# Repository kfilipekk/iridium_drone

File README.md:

# NAVCORE-SoOP

A 46.5 × 47.2 mm, 6-layer STM32H743 flight controller that navigates without GPS using the Doppler shift of Iridium satellites. It runs ArduPilot with a MatekH743-compatible pinout and also carries the avionics for a TVC rocket lander. Made by Krystian Filipek for my GNSS-denied drone and the Cambridge University Spaceflight Lander Challenge.

<div align="center">

</div>

## Features

### Iridium Navigation
Optical flow and visual-inertial odometry drift without bound over long flights. Iridium NEXT satellites orbit at ~780 km and ~7.5 km/s and transmit continuously at 1616-1626.5 MHz, so the Doppler shift of their bursts gives an absolute position with bounded error (typically 100-200 m) that complements the faster inertial sensors.

- **L-band Receiver** - MAX2112 direct-conversion tuner and OPA2374 baseband filter into the ADCs
- **Antenna Feed** - MMCX port with a current-limited 5 V feed for the active antenna, reported as open, ok or short
- **On-board Navigation** - burst detection, SGP4 orbits and the position solve run on the H743 and feed ArduPilot's EKF as a GPS
- **Spoofing Check** - the real GPS is checked against the Iridium-only fix before it is trusted

### Hardware
| Subsystem | Components |
|-----------|------------|
| MCU | STM32H743VIT6, Cortex-M7 @ 480 MHz, 2 MB flash, 1 MB RAM |
| IMUs | ICM-42688-P (SPI1) and ICM-42605 (SPI4) on a separate low-noise 3.3 V rail |
| Barometer | MS5611 on I2C2 |
| Storage | W25Q128 flash for the orbit catalogue, microSD over SDIO |
| Power | 3S-5S input, TVS and reverse-polarity protection, two LMR33630 bucks (5 V 1.6 A system, 5 V 2.1 A payload) and three 3.3 V LDOs |
| Connectors | Latching JST-GH on every cable port, two servo headers, MMCX, USB-C, TC2030 SWD pads |
| Protection | ESD clamp on every cable-facing signal, series resistors on the motor, telemetry, current, lidar and servo lines |

### Layer Stackup
```
F.Cu:   RF, crystals, MCU fanout
In1.Cu: Continuous ground plane
In2.Cu: SPI, SDIO and I2C
In3.Cu: UARTs, PWM and slow I/O
In4.Cu: Power planes (+5V, +5V_PAYLOAD, +3V3, VBAT)
B.Cu:   Sensors, RF receiver, DroneCAN, bucks
```

### Supported Platforms
- **GNSS-denied Quadcopter** - 30.5 mm stack mount, DShot ESC on `J2`, optical flow on `J14`, lidar on `J11`, companion computer on `J21`, DroneCAN on `J6`
- **TVC Rocket Lander** - two servo outputs (`J17`, `J23`) on the payload rail and 6-DoF logging to microSD

### How It Compares
| | NAVCORE-SoOP | SpeedyBee F405 V4 | Matek H743-SLIM V3 | Pixhawk 6C |
|---|---|---|---|---|
| MCU | STM32H743 | STM32F405 | STM32H743 | STM32H743 + F103 |
| IMUs | ICM-42688-P + ICM-42605 | ICM-42688-P | ICM-42688-P + ICM-42605 | ICM-42688-P + BMI088 |
| Input | 3-5S | 3-6S | 2-8S | power module |
| Port ESD | every cable signal | none stated | none stated | none stated |
| Position without GNSS | Iridium Doppler, 100-200 m | none | none | none |

It has no OSD and no 9-12 V video rail, and it takes 5S at most.

## Getting Started

### Prerequisites
- **KiCad 9** with the `pcbnew` Python module
- **Python 3** with `pip install -r requirements.txt`
- **[kicad-tools](https://github.com/kfilipekk/kicad-tools)** cloned to `~/Code/kicad-tools`, or set `KICAD_TOOLS` - the checks any board needs live there
- **ArduPilot toolchain** for the firmware (`tools/build_firmware.sh` pins Copter-4.7.0)

### Checking the Board
1. Clone the repository:
   ```bash
   git clone https://github.com/kfilipekk/iridium_drone.git
   cd iridium_drone
   ```

2. Run every check (about 15 minutes):
   ```bash
   python3 tools/preflight.py
   ```

3. Or run one check on its own:
   ```bash
   python3 tools/check_board.py connectors
   python3 ~/Code/kicad-tools/fab.py stock
   ```

4. Build the firmware:
   ```bash
   bash tools/build_firmware.sh
   ```

### Ordering
The JLCPCB files are in `fab/`: the Gerber and drill bundle, BOM, pick-and-place and schematic PDF. Order 6 layers, 1 oz outer copper, no impedance control, epoxy-filled and capped vias, ENIG, and top and bottom assembly.

## Repository Structure

```
├── NAVCORE-SoOP.kicad_pcb   # PCB
├── NAVCORE-SoOP.kicad_sch   # Schematic, generated from tools/design.py
├── fab/                     # JLCPCB order files
├── firmware/                # ArduPilot hwdef, the SoOP backend and the on-board navigation
├── tools/                   # Design model, generators and checks
├── cad/                     # OpenSCAD airframe and clearance models
├── sim/                     # SPICE decks for the analogue blocks
├── sitl/                    # ArduPilot SITL scenarios
└── libraries/               # Footprint and symbol libraries
```

## Applications

I made this project to explore:
- Navigation from signals of opportunity instead of GPS
- Six-layer mixed-signal PCB design with an RF front end
- ArduPilot drivers and EKF integration
- Automated checks for a hardware design

## Future Plans

- Bench-test the Iridium receive chain with the HC610 antenna
- Rev E: a third IMU, 6S input and a 9-12 V video rail

<div align="center">

Developed by [kfilipekk](https://github.com/kfilipekk)

</div>

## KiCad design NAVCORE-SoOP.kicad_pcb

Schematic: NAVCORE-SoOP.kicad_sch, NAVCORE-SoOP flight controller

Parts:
C1, C2, C3, C4, C5, C10, C12, C14, C21, C30, C31, C32, C33, C34, C35, C36, C41, C43, C44, C46, C49, C50, C57, C60, C65, C68, C74, C88, C89, C90, C94, C95, C96: 100n; C_0402_1005Metric; LCSC C1525
C6, C7: 4u7; C_0805_2012Metric; LCSC C354262
C8, C9, C29: 2u2; C_0402_1005Metric; LCSC C12530
C11, C13, C26, C27, C28, C51, C67, C75, C78, C79, C80: 1u; C_0402_1005Metric; LCSC C52923
C15, C16: 30p; C_0402_1005Metric; LCSC C107004
C17, C18: 10u; C_1206_3216Metric; LCSC C13585
C19, C66: 100n; C_0402_1005Metric; LCSC C307331
C22: 100u; C_1206_3216Metric; LCSC C883598
C23, C69, C70: 47u; C_1206_3216Metric; LCSC C96123
C42: 1u; C_0805_2012Metric; LCSC C28323
C45, C93: 10u; C_0805_2012Metric; LCSC C15850
C52: 33p; C_0402_1005Metric; LCSC C1562
C56, C98, C99: 100p; C_0201_0603Metric; LCSC C62550
C58, C73: 10n; C_0402_1005Metric; LCSC C15195
C59, C97: 100n; C_0201_0603Metric; LCSC C76939
C61, C63: 47n; C_0402_1005Metric; LCSC C82219
C76, C77: 100p; C_0402_1005Metric; LCSC C1546
C81, C84, C86: 1n; C_0402_1005Metric; LCSC C1523
C91: 10p; C_0402_1005Metric; LCSC C32949
C92: 22u; C_1206_3216Metric; LCSC C12891
C100, C101: 1n; C_0201_0603Metric; LCSC C710792
D1: SMBJ22CA; SMB_L4.6-W3.6-LS5.3-RD; LCSC C113994
D2: BLUE; LED_0603_1608Metric; LCSC C965807
D3: GREEN; LED_0603_1608Metric; LCSC C965804
D4: 1N4148W; SOD-123F_L2.7-W1.6-LS3.8-RD; LCSC C81598
D6: PESD2CANFD24LT; SOT-23-3_L2.9-W1.6-P1.90-LS2.8-BR; LCSC C6952426
D7, D9: PESD5V0C1BSF; DSN0603-2_L0.6-W0.3-P0.40-BI; LCSC C477955
D8: SMF9.0A; SOD-123FL_L2.7-W1.8-LS3.7-RD; LCSC C1973343
D10: B2020WS; SOD-323_L1.7-W1.3-LS2.7-RD; LCSC C77284
DZ1: BZT52C15; SOD-123_L2.7-W1.6-LS3.7-RD; LCSC C173427
D_USB: B5819W; SOD-123_L2.7-W1.6-LS3.7-RD-1; LCSC C8598
FID1, FID2, FID3: Fiducial; Fiducial_1mm_Mask2mm
J1: USB-C; USB-C-SMD_TYPE-C-16PIN-2MD-073; LCSC C2765186
J2: ESC 8P; CONN-TH_SM08B-SRSS-TB-LF-SN; LCSC C160407
J3: GPS+I2C; CONN-SMD_XY-SM06B-GHS-TB; LCSC C51940119
J5: RC IN; CONN-SMD_4P-P1.25_BX-GH1.25-4PWT; LCSC C18077720
J6: CAN 4P; CONN-SMD_4P-P1.25_BX-GH1.25-4PWT; LCSC C18077720
J8: microSD; TF-SMD_TF-01A; LCSC C91145
J9: I2C 4P; CONN-SMD_4P-P1.25_BX-GH1.25-4PWT; LCSC C18077720
J11: SERIAL2 4P; CONN-SMD_4P-P1.25_BX-GH1.25-4PWT; LCSC C18077720
J12: MMCX-KWE-90; MMCX-TH_DL-MMCX-KWE-90; LCSC C2894793
J14: FLOW 6P; CONN-SMD_XY-SM06B-GHS-TB; LCSC C51940119
J17: SERVO1; HDR-SMD_3P-P2.54-H-M_KH-2.54PH-1X3P-L13.5-WT; LCSC C20610212
J19: TC2030-NL; Tag-Connect_TC2030-IDC-NL_2x03_P1.27mm_Vertical
J21: COMPANION; CONN-SMD_XY-SM06B-GHS-TB; LCSC C51940119
J22: PAYLOAD 5V; CONN-TH_SM03B-GHS-TB-LF-SN; LCSC C514175
J23: SERVO2; HDR-SMD_3P-P2.54-H-M_KH-2.54PH-1X3P-L13.5-WT; LCSC C20610212
L1: 600R@100MHz; L_0805_2012Metric; LCSC C1017
L2: 10uH; L_APV_ANR4030; LCSC C167879
L5: 10uH; L_APV_ANR5040; LCSC C354610
L6: 27nH; L0402; LCSC C113111
P151: LED_5V; TestPoint_Pad_1.5x1.5mm
P152: LED_DIN; TestPoint_Pad_1.5x1.5mm
P153: LED_GND; TestPoint_Pad_1.5x1.5mm
P161: BUZ_5V; TestPoint_Pad_1.5x1.5mm
P162: BUZ_OUT; TestPoint_Pad_1.5x1.5mm
P163: BUZ_GND; TestPoint_Pad_1.5x1.5mm
PF1, PF2, PF3, PF4, PF5, PF6, PF7, PF9, PF10, PF11: PWR_FLAG
PF8: PWR_FLAG; not fitted
Q1, Q3: AO3400A; SOT-23-3_L2.9-W1.3-P1.90-LS2.4-BR; LCSC C20917
Q4: WST4041; SOT-23-3_L2.9-W1.3-P1.90-LS2.4-BR; LCSC C148357
R1, R14, R39, R45, R48, R49, R50, R51, R52, R53, R59, R60: 10k; R_0402_1005Metric; LCSC C25744
R4, R6, R40, R42, R46: 100k; R_0402_1005Metric; LCSC C25741
R5, R41: 22k; R_0402_1005Metric; LCSC C25768
R7, R43: 24k9; R_0402_1005Metric; LCSC C25874
R9, R10, R12, R31, R36, R37, R47, R58: 4k7; R_0402_1005Metric; LCSC C25900
R11: 4k7; R_0201_0603Metric; LCSC C270346
R15: 120R; R_0402_1005Metric; LCSC C25079; not fitted
R16, R17: 5k1; R_0402_1005Metric; LCSC C25905
R18: 10k; R_0603_1608Metric; LCSC C25804
R19, R20, R21, R35: 1k; R_0402_1005Metric; LCSC C11702
R22, R23, R24, R25, R26: 47k; R_0402_1005Metric; LCSC C25792
R27: 47k; R_0402_1005Metric; LCSC C25792; not fitted
R28, R29: 0R; R_0402_1005Metric; LCSC C17168
R34: 330R; R_0402_1005Metric; LCSC C25104
R38, R70, R72, R73, R74, R75: 100R; R_0402_1005Metric; LCSC C25076
R57: 470R; R_0402_1005Metric; LCSC C25117
R61: 210k; R_0402_1005Metric; LCSC C58827
R62: 2R2; R_0402_1005Metric; LCSC C1881139
R71: 2k2; R_0402_1005Metric; LCSC C25879
R76, R77: 680R; R_0201_0603Metric; LCSC C473509
RN1: 33R x4; R_Array_Convex_4x0402; LCSC C25501
SW1: BOOT; SW_SPST_B3U-1000P; LCSC C231329
SW2: RESET; SW_SPST_B3U-1000P; LCSC C231329
TP3: PWM5; TestPoint_Pad_1.5x1.5mm
TP4: PWM6; TestPoint_Pad_1.5x1.5mm
TP9: SOOP_I_OUT; TestPoint_Pad_1.5x1.5mm
TP10: SOOP_Q_OUT; TestPoint_Pad_1.5x1.5mm
U1: STM32H743VIT6; LQFP-100_L14.0-W14.0-P0.50-LS16.0-BL; LCSC C5271084
U2: ICM-45686; LGA-14_L3.0-W2.5-P0.50-TL; LCSC C22459454
U3: ICM-42605; LGA-14_L3.0-W2.5-P0.50-TL; LCSC C2655099
U4: MS5611; SENSORS-SMD_MS5611-01BA03; LCSC C15639
U5: W25Q128JVPIQ; WSON-8-1EP_6x5mm_P1.27mm_EP3.4x4.3mm; LCSC C190862
U8, U20: LMR33630A; VQFN-12_L3.0-W2.0-P0.65-BL_TI_RNX; LCSC C2861505
U9: TLV75733P; SOT-23-5_L2.9-W1.6-P0.95-LS2.8-BL-EP; LCSC C22399950
U10: TLV75533; SOT-23-5_L3.0-W1.7-P0.95-LS2.8-BR; LCSC C404027
U11: SN65HVD230; SOIC-8_L4.9-W3.9-P1.27-LS6.0-BL; LCSC C12084
U12: USBLC6-2SC6; SOT-23-6_L2.9-W1.6-P0.95-LS2.8-BL; LCSC C2687116
U13: MAX2112; TQFN-28_L5.0-W5.0-P0.50-BL-EP3.3; LCSC C596391
U14: OPA2374; SOP-8_L4.9-W3.9-P1.27-LS6.0-BL; LCSC C444392
U17: 74LVC1G17; SOT-23-5_L3.0-W1.7-P0.95-LS2.8-BR; LCSC C7836
U19: TMP119; DSBGA-6_L1.5-W1.0-R2-C3-P0.40-BL; LCSC C22428347
U21: XC6206P332MR; SOT-23-3_L2.9-W1.6-P1.90-LS2.8-BR; LCSC C5446
U22, U23: SRV05-4; SOT-23-6_L2.9-W1.6-P0.95-LS2.8-BR; LCSC C6454456
U24: AP22653; SOT-23-6_L2.9-W1.6-P0.95-LS2.8-BR; LCSC C2158037
U25: INA180A2; SOT-23-5_L3.0-W1.7-P0.95-LS2.8-BL; LCSC C192764
U26, U27, U28, U29, U30: TPD4E05U06; USON-10_2.5x1.0mm_P0.5mm; LCSC C138714
U31: LM66100; SC-70-6_L2.0-W1.3-P0.65-LS2.1-BL; LCSC C2869734
Y1: 8MHz; CRYSTAL-SMD_4P-L3.2-W2.5-BL; LCSC C2682774
Y2: 25MHz TCXO; OSC-SMD_4P-L3.2-W2.5-BL; LCSC C19674258

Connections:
+3V3A: C29.1, C30.1, C31.1, C32.1, C33.1, C34.1, C35.1, C59.1, C97.1, PF4.1, R11.1, R28.1, R52.1, U2.5 (VDDIO), U2.8 (VDD), U3.5 (VDDIO), U3.8 (VDD), U4.1 (VDD), U4.2 (PS), U10.5 (OUT), U14.8 (VCC+), Y2.4 (VCC)
+3V3_CAN: C41.1, C67.1, U11.3 (VCC), U21.2 (Vout)
+5V_BIAS: C90.1, C91.1, C93.1, L6.1, R62.2, U25.4 (IN-)
+5V_BIAS_SW: C96.1, R62.1, U24.6 (OUT), U25.3 (IN+)
ANT_CURRENT: U1.17 (PC2_C), U25.1 (OUT)
ANT_IN: C52.1, D7.1 (A1), J12.1 (SIG), L6.2
BATT_V_DIV: C43.1, R18.2, R19.1, U1.15 (PC0)
BB_VREF: C75.1, C98.2, C99.2, R49.2, R51.2, R52.2, R53.1
BIAS_EN: R59.2, U1.33 (PC5), U24.3 (EN/EN#)
BIAS_FAULT: R60.2, U1.57 (PD10), U24.4 (FAULT#)
BIAS_ILIM: R61.1, U24.5 (ILIM)
BOOT0: R1.1, SW1.2, U1.94 (BOOT0)
BUCK_BOOT: C21.1, U8.4 (BOOT)
BUCK_EN: R4.2, R5.1, U8.9 (EN)
BUCK_FB: R6.2, R7.1, U8.7 (FB)
BUCK_PAYLOAD_BOOT: C68.1, U20.4 (BOOT)
BUCK_PAYLOAD_EN: C73.1, Q3.3 (D), R40.2, R41.1, U20.9 (EN)
BUCK_PAYLOAD_FB: R42.2, R43.1, U20.7 (FB)
BUCK_PAYLOAD_PH: C68.2, L5.1, U20.3 (NC), U20.12 (SW)
BUCK_PAYLOAD_VCC: C79.1, U20.5 (VCC)
BUCK_PH: C21.2, L2.1, U8.3 (NC), U8.12 (SW)
BUCK_VCC: C78.1, U8.5 (VCC)
BUZZER: R38.1, U1.77 (PA15)
BUZZ_DRAIN: D4.2 (A), P162.1, Q1.3 (D)
BUZZ_GATE: Q1.1 (G), R38.2, R39.1
CAN1_RX: U1.81 (PD0), U11.4 (R)
CAN1_SILENT: R14.1, U1.84 (PD3), U11.8 (RS)
CAN1_TX: U1.82 (PD1), U11.1 (D)
CANH: D6.1 (C), J6.2, R15.1, U11.7 (CANH)
CANL: D6.2 (C), J6.3, R15.2, U11.6 (CANL)
CC1: J1.A5 (CC1), R16.1
CC2: J1.B5 (CC2), R17.1
CPOUT: C81.1, R34.1, R57.1, U13.12 (CPOUT)
ESC_CUR: C44.1, R71.2, U1.16 (PC1)
ESC_CUR_J: J2.7, R71.1, U27.1 (D1+), U27.10 (NC)
ESC_TEL: R70.2, U1.97 (PE0)
ESC_TEL_J: J2.8, R70.1, U27.2 (D1-), U27.9 (NC)
EXT_CS1: J14.5, U1.7 (PC13), U29.5 (D2-), U29.6 (NC)
EXT_CS2: U1.1 (PE2), U5.1 (#CS)
GC1: R35.2, R58.2, U13.5 (GC1)
GND: C1.2, C2.2, C3.2, C4.2, C5.2, C6.2, C7.2, C8.2, C9.2, C10.2, C11.2, C12.2, C13.2, C14.2, C15.2, C16.2, C17.2, C18.2, C19.2, C22.2, C23.2, C26.2, C27.2, C28.2, C29.2, C30.2, C31.2, C32.2, C33.2, C34.2, C35.2, C36.2, C41.2, C42.2, C43.2, C44.2, C45.2, C46.2, C49.2, C50.2, C51.2, C56.2, C57.2, C59.2, C60.2, C65.2, C66.2, C67.2, C69.2, C70.2, C73.2, C74.2, C75.2, C78.2, C79.2, C80.2, C81.2, C84.2, C86.2, C88.2, C89.2, C90.2, C91.2, C92.2, C93.2, C94.2, C95.2, C96.2, C97.2, C100.2, C101.2, D1.2 (A2), D6.3 (A), D7.2 (A2), D8.2, D9.2 (A2), J1.13 (EH), J1.14 (EH), J1.A1B12 (GND), J1.B1A12 (GND), J2.1, J2.9, J2.10, J3.6, J3.7, J3.8, J5.4, J5.5, J5.6, J6.4, J6.5, J6.6, J8.6 (VSS), J8.10 (GND), J8.11 (GND), J8.12 (GND), J8.13 (GND), J9.4, J9.5, J9.6, J11.4, J11.5, J11.6, J12.2 (GND), J12.3 (GND), J12.4 (GND), J12.5 (GND), J14.6, J14.7, J14.8, J17.3, J19.5, J19.6, J21.6, J21.7, J21.8, J22.2, J22.3, J22.4, J22.5, J23.3, P153.1, P163.1, PF5.1, Q1.2 (S), Q3.2 (S), R1.2, R5.2, R7.2, R14.2, R16.2, R17.2, R19.2, R29.1, R35.1, R39.2, R41.2, R43.2, R45.2, R46.2, R53.2, R61.2, SW2.2, U1.10 (VSS), U1.19 (VSSA), U1.26 (VSS), U1.49 (VSS), U1.74 (VSS), U1.99 (VSS), U2.6 (GND), U2.7 (RESV), U3.6 (GND), U3.7 (RESV), U4.3 (GND), U4.4 (CSB), U4.5 (CSB), U5.4 (GND), U5.9 (EP), U8.1 (PGND), U8.6 (AGND), U8.11 (PGND), U9.2 (GND), U9.6 (EP), U10.2 (GND), U11.2 (GND), U12.2 (GND), U13.3 (GND), U13.10 (GNDTUNE), U13.11 (GNDSYN), U13.29 (EP), U14.4 (VCC-), U17.3 (GND), U19.B2 (GND), U19.C1 (ADD0), U20.1 (PGND), U20.6 (AGND), U20.11 (PGND), U21.1 (GND), U22.2 (GND), U23.2 (GND), U24.2 (GND), U25.2 (GND), U26.3 (GND), U26.8 (GND), U27.3 (GND), U27.8 (GND), U28.3 (GND), U28.8 (GND), U29.3 (GND), U29.8 (GND), U30.3 (GND), U30.8 (GND), U31.2 (GND), U31.4 (NC), U31.5 (ST), Y1.2 (GND), Y1.4 (GND), Y2.1 (GND or N.C.), Y2.2 (GND)
I2C1_SCL: J3.4, J9.2, R9.2, U1.92 (PB6), U19.A2 (SCL), U22.4 (IO3)
I2C1_SDA: J3.5, J9.3, R10.2, U1.93 (PB7), U19.A1 (SDA), U22.6 (IO4)
I2C2_SCL: R11.2, U1.46 (PB10), U4.8 (SCLK), U13.27 (SCL)
I2C2_SDA: R12.2, U1.47 (PB11), U4.7 (SDI/SDA), U13.26 (SDA)
IDC_N: C61.2, U13.22 (IDC-)
IDC_P: C61.1, U13.21 (IDC+)
IMU1_CS: U1.9 (PC15-OSC32_OUT), U2.12 (AP_CS)
IMU2_CS: U1.41 (PE11), U3.12 (AP_CS)
IOUT_N: R37.1, U13.20 (IOUT-)
IOUT_P: R36.1, U13.19 (IOUT+)
LED0: R20.2, U1.2 (PE3)
LED0_K: D2.1 (K), R20.1
LED1: R21.2, U1.3 (PE4)
LED1_K: D3.1 (K), R21.1
LOOP: C57.1, R34.2
M1: RN1.4 (R4.1), U1.34 (PB0)
M1_J: J2.3, RN1.5 (R4.2), U26.1 (D1+), U26.10 (NC)
M2: RN1.3 (R3.1), U1.35 (PB1)
M2_J: J2.4, RN1.6 (R3.2), U26.2 (D1-), U26.9 (NC)
M3: RN1.2 (R2.1), U1.22 (PA0)
M3_J: J2.5, RN1.7 (R2.2), U26.4 (D2+), U26.7 (NC)
M4: RN1.1 (R1.1), U1.23 (PA1)
M4_J: J2.6, RN1.8 (R1.2), U26.5 (D2-), U26.6 (NC)
NRST: C14.1, J19.3, SW2.1, U1.14 (NRST)
OPA_IN1N: C76.1, R37.2, R50.1, U14.2 (IN1-)
OPA_IN1P: C98.1, R36.2, R51.1, U14.3 (IN1+)
OPA_IN2N: C77.1, R31.2, R48.1, U14.6 (IN2-)
OPA_IN2P: C99.1, R47.2, R49.1, U14.5 (IN2+)
OSC_IN: C15.1, U1.12 (PH0-OSC_IN), Y1.1
OSC_OUT: C16.1, U1.13 (PH1-OSC_OUT), Y1.3
PAYLOAD_EN: Q3.1 (G), R45.1, U1.31 (PA7)
PWM5: TP3.1, U1.96 (PB9)
PWM6: TP4.1, U1.25 (PA3)
PWM7: R75.2, U1.95 (PB8)
PWM7_J: D9.1 (A1), J17.1, R75.1
PWM8: R74.2, U1.60 (PD13)
PWM8_J: J23.1, R74.1, U30.4 (D2+), U30.7 (NC)
QDC_N: C63.2, U13.24 (QDC-)
QDC_P: C63.1, U13.23 (QDC+)
QOUT_N: R31.1, U13.18 (QOUT-)
QOUT_P: R47.1, U13.17 (QOUT+)
RC_IN: J5.3, U1.64 (PC7), U23.3 (IO2)
RFIN: C52.2, U13.4 (RFIN)
SD_CD: J8.9 (CD), R27.2
SD_CK: J8.5 (CLK(SCLK)), U1.80 (PC12)
SD_CMD: J8.3 (CMD(DI)), R26.2, U1.83 (PD2)
SD_D0: J8.7 (DAT0(D0)), R22.2, U1.65 (PC8)
SD_D1: J8.8 (DAT1(RSV)), R23.2, U1.66 (PC9)
SD_D2: J8.1 (DAT2(RSV)), R24.2, U1.78 (PC10)
SD_D3: J8.2 (CDDAT3(CS)), R25.2, U1.79 (PC11)
SPI1_MISO: U1.30 (PA6), U2.1 (AP_SDO/AP_AD0)
SPI1_MOSI: U1.88 (PD7), U2.14 (AP_SDA/AP_SDIO/AP_SDI)
SPI1_SCK: U1.29 (PA5), U2.13 (AP_SCL/AP_SCLK)
SPI3_MISO: J14.3, U1.90 (PB4), U5.2 (DO/IO1), U29.2 (D1-), U29.9 (NC)
SPI3_MOSI: J14.4, U1.91 (PB5), U5.5 (DI/IO0), U29.4 (D2+), U29.7 (NC)
SPI3_SCK: J14.2, U1.89 (PB3), U5.6 (CLK), U29.1 (D1+), U29.10 (NC)
SPI4_MISO: U1.43 (PE13), U3.1 (AP_SDO/AP_AD0)
SPI4_MOSI: U1.44 (PE14), U3.14 (AP_SDA/AP_SDIO/AP_SDI)
SPI4_SCK: U1.42 (PE12), U3.13 (AP_SCL/AP_SCLK)
SWCLK: J19.4, U1.76 (PA14)
SWDIO: J19.2, U1.72 (PA13)
TUNER_ADDR: R29.2, U13.28 (ADDR)
TUNER_REF: C58.1, Y2.3 (OUTPUT RF)
TUNER_XTAL: C58.2, U13.14 (XTAL)
UART7_CTS: J21.4, U1.40 (PE10), U28.4 (D2+), U28.7 (NC)
UART7_RTS: J21.5, U1.39 (PE9), U28.5 (D2-), U28.6 (NC)
UART7_RX: J21.3, U1.37 (PE7), U28.2 (D1-), U28.9 (NC)
UART7_TX: J21.2, U1.38 (PE8), U28.1 (D1+), U28.10 (NC)
USART1_RX: R73.2, U1.69 (PA10)
USART1_RX_J: J11.3, R73.1, U30.2 (D1-), U30.9 (NC)
USART1_TX: R72.2, U1.68 (PA9)
USART1_TX_J: J11.2, R72.1, U30.1 (D1+), U30.10 (NC)
USART2_RX: J3.3, U1.87 (PD6), U22.3 (IO2)
USART2_TX: J3.2, U1.86 (PD5), U22.1 (IO1)
USART6_TX: J5.2, U1.63 (PC6), U23.1 (IO1)
USB_DM: U1.70 (PA11), U12.4 (I/O2)
USB_DM_CON: J1.A7 (Dn1), J1.B7 (Dn2), U12.3 (I/O2)
USB_DP: U1.71 (PA12), U12.6 (I/O1)
USB_DP_CON: J1.A6 (Dp1), J1.B6 (Dp2), U12.1 (I/O1)
VBAT: C17.1, C18.1, C19.1, C66.1, DZ1.1 (K), PF1.1, Q4.2 (S), R4.1, R18.1, R40.1, U8.2 (VIN), U8.10 (VIN), U20.2 (VIN), U20.10 (VIN)
VBAT_GATE: DZ1.2 (A), Q4.1 (G), R46.1
VBAT_IN: D1.1 (A1), J2.2, PF9.1, Q4.3 (D)
VBUS: C42.1, D_USB.2 (+), J1.A4B9 (VBUS), J1.B4A9 (VBUS), PF7.1, U12.5 (VBUS)
VCAP1: C8.1, U1.48 (VCAP)
VCAP2: C9.1, U1.73 (VCAP)
VCC_RF: C49.1, C50.1, C51.1, C84.1, C86.1, PF8.1, R28.2, R58.1, U13.1 (VCC_RF2), U13.2 (VCC_RF1), U13.6 (VCC_LO), U13.7 (VCC_VCO), U13.13 (VCC_SYN), U13.16 (VCC_DIG), U13.25 (VCC_BB)
VCOBYP: C60.1, U13.8 (VCOBYP)
VDDA: C10.1, C11.1, C12.1, C13.1, L1.2, PF6.1, U1.20 (VREF+), U1.21 (VDDA)
VTUNE: C56.1, R57.2, U13.9 (VTUNE)
WS2812: U1.67 (PA8), U17.2 (A)
WS2812_OUT: P152.1, U17.4 (Y)

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
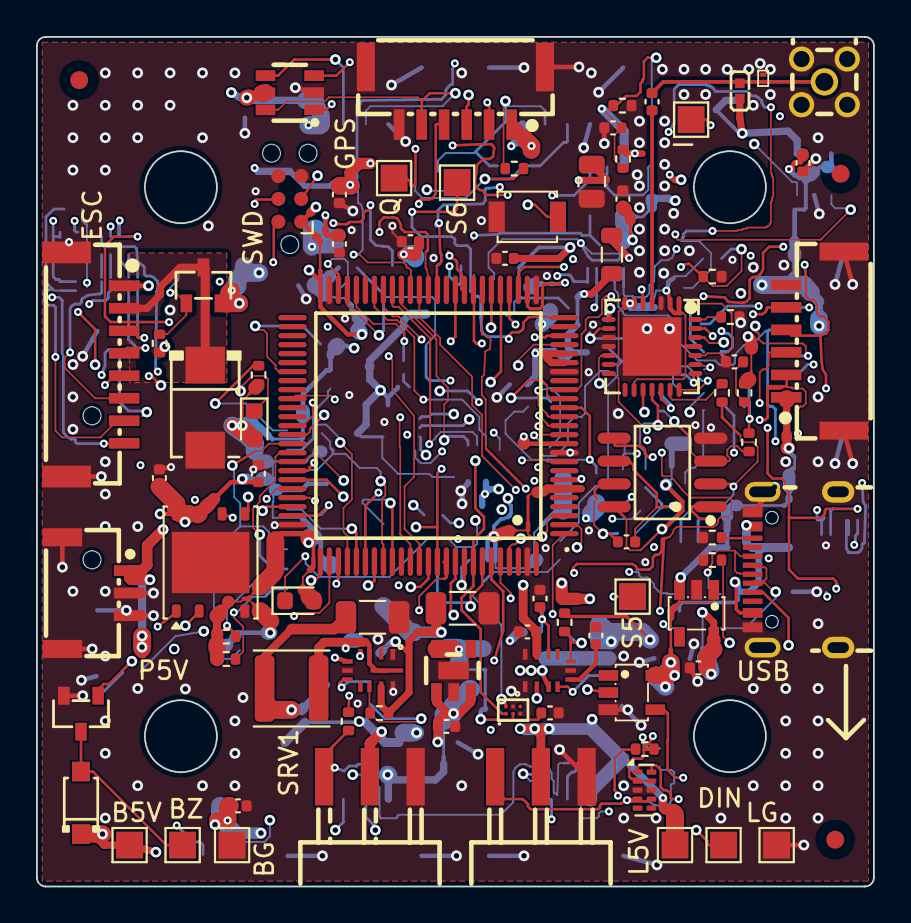
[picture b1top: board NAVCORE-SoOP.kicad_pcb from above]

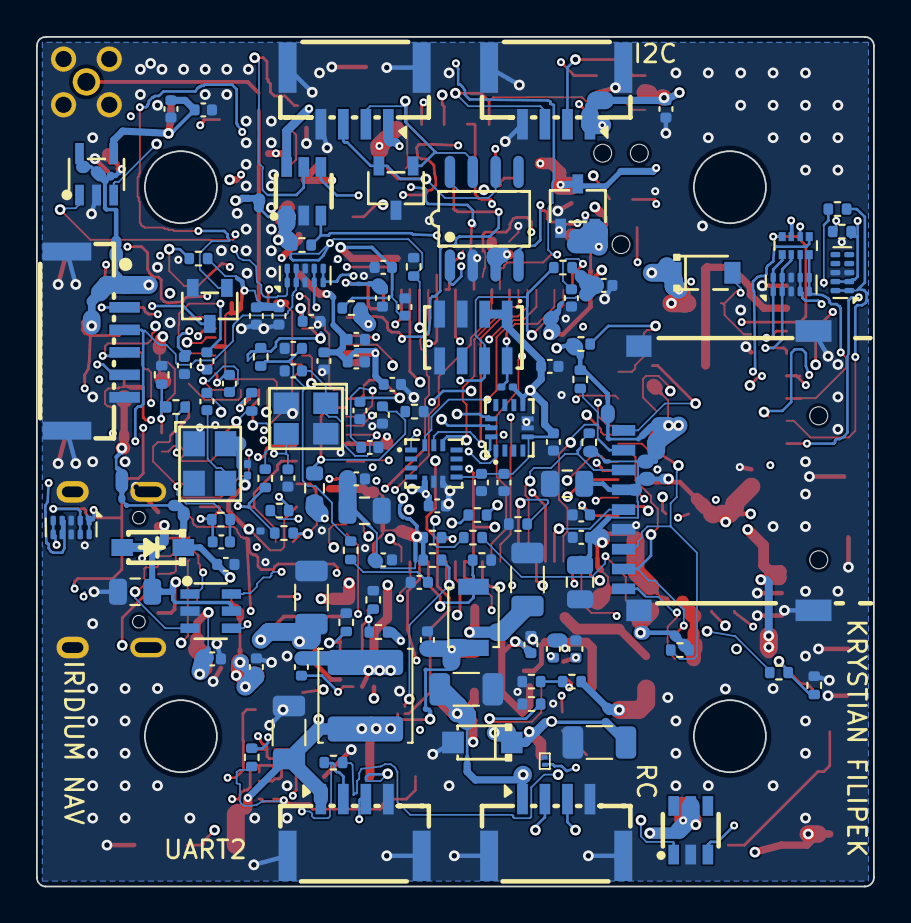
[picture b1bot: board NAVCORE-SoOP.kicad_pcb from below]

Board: 6 copper layers, 46.5 x 47.2 mm, 209 parts (124 on the bottom side), 137 nets.

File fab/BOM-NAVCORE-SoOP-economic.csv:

Comment,Designator,Footprint,LCSC,Qty,DNP
100n,"C1,C10,C12,C14,C2,C21,C3,C30,C31,C32,C33,C34,C35,C36,C4,C41,C43,C44,C46,C49,C5,C50,C57,C60,C65,C68,C74,C88,C89,C90,C94,C95,C96",C_0402_1005Metric,C1525,33,
10k,"R1,R14,R39,R45,R48,R49,R50,R51,R52,R53,R59,R60",R_0402_1005Metric,C25744,12,
1u,"C11,C13,C26,C27,C28,C51,C67,C75,C78,C79,C80",C_0402_1005Metric,C52923,11,
4k7,"R10,R12,R31,R36,R37,R47,R58,R9",R_0402_1005Metric,C25900,8,
100R,"R38,R70,R72,R73,R74,R75",R_0402_1005Metric,C25076,6,
100k,"R4,R40,R42,R46,R6",R_0402_1005Metric,C25741,5,
47k,"R22,R23,R24,R25,R26",R_0402_1005Metric,C25792,5,
TPD4E05U06,"U26,U27,U28,U29,U30",USON-10_2.5x1.0mm_P0.5mm,C138714,5,
1k,"R19,R20,R21,R35",R_0402_1005Metric,C11702,4,
2u2,"C29,C8,C9",C_0402_1005Metric,C12530,3,
47u,"C23,C69,C70",C_1206_3216Metric,C96123,3,
100p,"C56,C98,C99",C_0201_0603Metric,C62550,3,
1n,"C81,C84,C86",C_0402_1005Metric,C1523,3,
LMR33630A,"U20,U8",VQFN-12_L3.0-W2.0-P0.65-BL_TI_RNX,C2861505,2,
4u7,"C6,C7",C_0805_2012Metric,C354262,2,
30p,"C15,C16",C_0402_1005Metric,C107004,2,
10u,"C17,C18",C_1206_3216Metric,C13585,2,
100n,"C19,C66",C_0402_1005Metric,C307331,2,
22k,"R41,R5",R_0402_1005Metric,C25768,2,
24k9,"R43,R7",R_0402_1005Metric,C25874,2,
5k1,"R16,R17",R_0402_1005Metric,C25905,2,
10u,"C45,C93",C_0805_2012Metric,C15850,2,
0R,"R28,R29",R_0402_1005Metric,C17168,2,
10n,"C58,C73",C_0402_1005Metric,C15195,2,
100n,"C59,C97",C_0201_0603Metric,C76939,2,
100p,"C76,C77",C_0402_1005Metric,C1546,2,
680R,"R76,R77",R_0201_0603Metric,C473509,2,
1n,"C100,C101",C_0201_0603Metric,C710792,2,
47n,"C61,C63",C_0402_1005Metric,C82219,2,
AO3400A,"Q1,Q3",SOT-23-3_L2.9-W1.3-P1.90-LS2.4-BR,C20917,2,
SRV05-4,"U22,U23",SOT-23-6_L2.9-W1.6-P0.95-LS2.8-BR,C6454456,2,
PESD5V0C1BSF,"D7,D9",DSN0603-2_L0.6-W0.3-P0.40-BI,C477955,2,
STM32H743VIT6,U1,LQFP-100_L14.0-W14.0-P0.50-LS16.0-BL,C5271084,1,
ICM-45686,U2,LGA-14_L3.0-W2.5-P0.50-TL,C22459454,1,
ICM-42605,U3,LGA-14_L3.0-W2.5-P0.50-TL,C2655099,1,DNP
MS5611,U4,SENSORS-SMD_MS5611-01BA03,C15639,1,
W25Q128JVPIQ,U5,WSON-8-1EP_6x5mm_P1.27mm_EP3.4x4.3mm,C190862,1,
TLV75733P,U9,SOT-23-5_L2.9-W1.6-P0.95-LS2.8-BL-EP,C22399950,1,
TLV75533,U10,SOT-23-5_L3.0-W1.7-P0.95-LS2.8-BR,C404027,1,
SN65HVD230,U11,SOIC-8_L4.9-W3.9-P1.27-LS6.0-BL,C12084,1,
USBLC6-2SC6,U12,SOT-23-6_L2.9-W1.6-P0.95-LS2.8-BL,C2687116,1,
USB-C,J1,USB-C-SMD_TYPE-C-16PIN-2MD-073,C2765186,1,
ESC 8P,J2,CONN-TH_SM08B-SRSS-TB-LF-SN,C160407,1,
GPS+I2C,J3,CONN-SMD_XY-SM06B-GHS-TB,C51940119,1,
RC IN,J5,CONN-SMD_4P-P1.25_BX-GH1.25-4PWT,C18077720,1,
CAN 4P,J6,CONN-SMD_4P-P1.25_BX-GH1.25-4PWT,C18077720,1,
microSD,J8,TF-SMD_TF-01A,C91145,1,
8MHz,Y1,CRYSTAL-SMD_4P-L3.2-W2.5-BL,C2682774,1,
SMBJ22CA,D1,SMB_L4.6-W3.6-LS5.3-RD,C113994,1,
MAX2112,U13,TQFN-28_L5.0-W5.0-P0.50-BL-EP3.3,C596391,1,
OPA2374,U14,SOP-8_L4.9-W3.9-P1.27-LS6.0-BL,C444392,1,
25MHz TCXO,Y2,OSC-SMD_4P-L3.2-W2.5-BL,C19674258,1,
600R@100MHz,L1,L_0805_2012Metric,C1017,1,
10uH,L2,L_APV_ANR4030,C167879,1,
100u,C22,C_1206_3216Metric,C883598,1,
4k7,R11,R_0201_0603Metric,C270346,1,
120R,R15,R_0402_1005Metric,C25079,1,DNP
1u,C42,C_0805_2012Metric,C28323,1,
10k,R18,R_0603_1608Metric,C25804,1,
BLUE,D2,LED_0603_1608Metric,C965807,1,
GREEN,D3,LED_0603_1608Metric,C965804,1,
BOOT,SW1,SW_SPST_B3U-1000P,C231329,1,
RESET,SW2,SW_SPST_B3U-1000P,C231329,1,
47k,R27,R_0402_1005Metric,C25792,1,DNP
33p,C52,C_0402_1005Metric,C1562,1,
330R,R34,R_0402_1005Metric,C25104,1,
470R,R57,R_0402_1005Metric,C25117,1,
LM66100,U31,SC-70-6_L2.0-W1.3-P0.65-LS2.1-BL,C2869734,1,
COMPANION,J21,CONN-SMD_XY-SM06B-GHS-TB,C51940119,1,
1N4148W,D4,SOD-123F_L2.7-W1.6-LS3.8-RD,C81598,1,
10uH,L5,L_APV_ANR5040,C354610,1,
PAYLOAD 5V,J22,CONN-TH_SM03B-GHS-TB-LF-SN,C514175,1,
74LVC1G17,U17,SOT-23-5_L3.0-W1.7-P0.95-LS2.8-BR,C7836,1,
XC6206P332MR,U21,SOT-23-3_L2.9-W1.6-P1.90-LS2.8-BR,C5446,1,
PESD2CANFD24LT,D6,SOT-23-3_L2.9-W1.6-P1.90-LS2.8-BR,C6952426,1,
FLOW 6P,J14,CONN-SMD_XY-SM06B-GHS-TB,C51940119,1,
SERVO1,J17,HDR-SMD_3P-P2.54-H-M_KH-2.54PH-1X3P-L13.5-WT,C20610212,1,
SERVO2,J23,HDR-SMD_3P-P2.54-H-M_KH-2.54PH-1X3P-L13.5-WT,C20610212,1,
B2020WS,D10,SOD-323_L1.7-W1.3-LS2.7-RD,C77284,1,
SMF9.0A,D8,SOD-123FL_L2.7-W1.8-LS3.7-RD,C1973343,1,
22u,C92,C_1206_3216Metric,C12891,1,
AP22653,U24,SOT-23-6_L2.9-W1.6-P0.95-LS2.8-BR,C2158037,1,
210k,R61,R_0402_1005Metric,C58827,1,
2R2,R62,R_0402_1005Metric,C1881139,1,
INA180A2,U25,SOT-23-5_L3.0-W1.7-P0.95-LS2.8-BL,C192764,1,
10p,C91,C_0402_1005Metric,C32949,1,
27nH,L6,L0402,C113111,1,
B5819W,D_USB,SOD-123_L2.7-W1.6-LS3.7-RD-1,C8598,1,
MMCX-KWE-90,J12,MMCX-TH_DL-MMCX-KWE-90,C2894793,1,
TMP119,U19,DSBGA-6_L1.5-W1.0-R2-C3-P0.40-BL,C22428347,1,
WST4041,Q4,SOT-23-3_L2.9-W1.3-P1.90-LS2.4-BR,C148357,1,
BZT52C15,DZ1,SOD-123_L2.7-W1.6-LS3.7-RD,C173427,1,
I2C 4P,J9,CONN-SMD_4P-P1.25_BX-GH1.25-4PWT,C18077720,1,
SERIAL2 4P,J11,CONN-SMD_4P-P1.25_BX-GH1.25-4PWT,C18077720,1,
33R x4,RN1,R_Array_Convex_4x0402,C25501,1,
2k2,R71,R_0402_1005Metric,C25879,1,

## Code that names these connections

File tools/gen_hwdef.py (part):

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    (r'^define OSD_ENABLED',     "no analogue OSD fitted"),
    (r'^define HAL_OSD_TYPE_DEFAULT', "no analogue OSD fitted"),
    (r'^ROMFS_WILDCARD libraries/AP_OSD', "no analogue OSD fitted"),
    (r'^PA4 BATT2_VOLTAGE_SENS', "single battery; freed for the SoOP I/Q input"),
    (r'^define HAL_BATT2_',      "single battery"),
    (r'^define HAL_DEFAULT_AIRSPEED_PIN', "no airspeed sensor"),
    (r'^define BOARD_RSSI_ANA_PIN', "RSSI arrives over CRSF"),
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    (r'^IMU Invensense SPI:mpu6000',  "MPU6000 not fitted"),
    (r'^SPIDEV icm20602',        "ICM-20602 not fitted"),
    (r'^SPIDEV mpu6000',         "MPU6000 not fitted"),
    (r'^PC7 TIM3_CH2 TIM3 RCININT',
     "RC is CRSF over USART6 (SERIAL7_PROTOCOL 23), so the timer input on the same pin goes, "
     "and TIM3 drives M1/M2 instead (PPM/SBUS-by-timer receivers lose their input)"),
    (r'^PB13 SPI2_SCK',          "SPI2 served only the analogue OSD, which is not fitted"),
    (r'^PB14 SPI2_MISO',         "SPI2 served only the analogue OSD, which is not fitted"),
    (r'^PB15 SPI2_MOSI',         "SPI2 served only the analogue OSD, which is not fitted"),
    (r'^PC13 IMU3_CS',           "no third IMU fitted; PC13 is the flow port's chip select"),
    (r'^PB9 UART4_TX',           "UART4 was never brought out; PB8 now carries servo PWM7"),
    (r'^PB8 UART4_RX',           "UART4 was never brought out; PB8 now carries servo PWM7"),
    (r'^PD14 TIM4_CH3',          "PWM9 had no connector; TIM4_CH3 is PWM7's on PB8"),
    (r'^PD15 TIM4_CH4',          "PWM10 had no connector; TIM4_CH4 is PWM5's on PB9"),
    (r'^PE1 UART8_TX',
     "ESC telemetry is receive-only, so UART8 needs only PE0/RX. PE1 is left "
     "unwired rather than declared and unconnected"),
]

#lines to rewrite: pins MatekH743 uses for something else
REPLACE = [
    (r'^PA7 BATT2_CURRENT_SENS',
     "PA7 PAYLOAD_EN OUTPUT LOW GPIO(83)",
     "MatekH743 reads PA7 as BATT2_CURRENT_SENS. This board has one battery, so the pin "
     "was free, and it now drives Q3's gate to switch the 5 V Payload rail (U20). LOW leaves "
     "the rail enabled - R45 pulls the gate down as well - so payload fails safe towards "
     "powered. It is deliberately a pin MatekH743 only ever READS: a stock MatekH743 "
     "binary cannot assert it and so cannot cut payload power."),
    (r'^PC4 PRESSURE_SENS ADC1 SCALE\(2\)',
     "PC4 SOOP_I_ADC ADC1 SCALE(1)",
     "No airspeed sensor: PC4 is the tuner's I, through the OPA2374 stage. Declared on ADC1 so "
     "the DMA resolver gives ADC1/ADC2 a stream of their own; AnalogIn leaves ADC1 alone "
     "(tools/install_soop_backend.py) and AP_SoOP_Capture samples it with Q on ADC2."),
    (r'^PC0 BATT_VOLTAGE_SENS ADC1 SCALE\(1\)',
     "PC0 BATT_VOLTAGE_SENS ADC3 SCALE(1)",
     "Battery sensing moves to ADC3 (PC0 is ADC123_INP10, the same channel number), so "
     "ADC1 and ADC2 are free to sample the tuner's I and Q together - AP_SoOP_Capture."),
    (r'^PC1 BATT_CURRENT_SENS ADC1 SCALE\(1\)',
     "PC1 BATT_CURRENT_SENS ADC3 SCALE(1)",
     "Battery current moves to ADC3 with the voltage (PC1 is ADC123_INP11)."),
    (r'^PC5 RSSI_ADC.*',
     "PC5 BIAS_EN OUTPUT HIGH GPIO(84)",
     "RSSI arrives over CRSF, so PC5 enables U24, the antenna's bias feed. HIGH, and R59 "
     "pulls it up, so the feed is on from power-up; AP_SoOP switches it off on a lasting "
     "short or when soop.cfg says ant_feed 0."),
    (r'^PD4 EXT_CS1 CS',
     "PC13 EXT_CS1 CS",
     "The flow port's chip select leaves PD4, on U1's north-west corner, for PC13 on the east "
     "side facing J14 and its clamp U29: the long run across the board would not route. "
     "PC13 is a low-drive RTC-domain pin (3 mA, 2 MHz), which a chip select that toggles once "
     "per transaction does not notice."),
    (r'^PD12 TIM4_CH1 TIM4 PWM\(7\) GPIO\(56\)',
     "PB8 TIM4_CH3 TIM4 PWM(7) GPIO(56)",
     "Servo 1 (J17) moves from PD12 on U1's west side to PB8 on the south edge, nearer J17: "
     "the run round U1 would not route. Same timer (TIM4) as PWM8, so the two servos keep "
     "one rate group."),
    (r'^PA2\s+TIM5_CH3\s+TIM5\s+PWM\(5\)\s+GPIO\(54\)',
     "PB9 TIM4_CH4 TIM4 PWM(5) GPIO(54)",
     "The spare servo output on test pad TP3 moves from PA2, whose escape faces the RF corner, "
     "to PB9 on U1's south edge beside TP3. It joins the servos' TIM4 rate group, and leaves "
     "TIM5 to the motors."),
    (r'^SERIAL_ORDER .*',
     "SERIAL_ORDER OTG1 UART7 USART1 USART2 USART3 UART8 EMPTY USART6 OTG2",
     "UART4 gave PB8 to PWM7. EMPTY keeps every other SERIALn where MatekH743 has it."),
    (r'^PD10\s+PINIO1.*',
     "PD10 BIAS_FAULT INPUT GPIO(85)",
     "U24's FAULT#, open drain, pulled up by R60: low on overcurrent, overtemperature or "
     "reverse voltage."),
    (r'^PD11\s+PINIO2.*',
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
#timers: same pins, other timers
REPLACE += [
    (r'^PB0\s+TIM8_CH2N.*', "PB0  TIM3_CH3 TIM3  PWM(1)  GPIO(50) BIDIR",
     "M1 moves from TIM8_CH2N (complementary - no input capture, so no BDShot) to TIM3_CH3 "
     "on the same pin, as MatekH743-bdshot does. BIDIR is set on the first channel of each "
     "pair, which reads for both."),
    (r'^PB1\s+TIM8_CH3N.*', "PB1  TIM3_CH4 TIM3  PWM(2)  GPIO(51)", "M2: TIM3_CH4, same pin."),
    (r'^PA0\s+TIM5_CH1.*', "PA0  TIM5_CH1  TIM5  PWM(3)  GPIO(52) BIDIR",
     "M3/M4 stay on TIM5 (MatekH743-bdshot moves them to TIM2, but TIM2_CH1 is the passive "
     "buzzer's tone on PA15)."),
    (r'^PC7 USART6_RX USART6 NODMA ALT\(1\)', "PC7 USART6_RX USART6 NODMA",
     "USART6_RX is PC7's only function now that the timer RC input is gone."),
    (r'^DMA_NOSHARE SPI1\* SPI4\*$', "DMA_NOSHARE SPI1* SPI4* TIM3* TIM5*",
     "the BDShot timers get DMA streams of their own, as the IMU buses do"),
]
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# U19, the TMP119 beside U9, needs this line or it is dead SILICON.
define AP_TEMPERATURE_SENSOR_ENABLED 1

# ADC1 samples the tuner's I (PC4, INP4) and ADC2 its Q (PA4, INP18) at the same instant, in
# dual regular-simultaneous mode, for the on-board Iridium navigation (AP_SoOP_Capture).
# Dual mode needs 32-bit ADC12 samples; the battery is on ADC3, above.
define STM32_ADC_DUAL_MODE TRUE
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    return f"""
# The antenna feed's current: U25 (INA180A2, x{a['gain']:.0f}) across R62 ({v} ohm), on PC2_C.
# PC2_C reaches ADC3_INP0 with its analogue switch open; AP_SoOP opens it (SYSCFG PMCR).
PC2 ANT_CURRENT ADC3 SCALE(1)
define HAL_SOOP_ANT_ADC_PIN 0
define HAL_SOOP_ANT_SENSE_OHM {ohm}f
define HAL_SOOP_ANT_GAIN {a['gain']:.1f}f
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
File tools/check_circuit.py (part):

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        return named[0]['num'], None
    if len(named) > 1:
        return None, f"pin name '{pinspec}' is ambiguous on {symname} ({len(named)} matches)"
    #allow "PC15" to match a pin named "PC15-OSC32_OUT"
    pre = [p for p in pins if p['name'].split('-')[0] == pinspec]
    if len(pre) == 1:
        return pre[0]['num'], None
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    gpio_used = {u.split('-')[0] for u in gpio_used}
    hwdef_pins = set(hw)
    missing = sorted(hwdef_pins - gpio_used)
    OUTSIDE_HWDEF = {"PH0","PH1",          #HSE crystal - hwdef declares OSCILLATOR_HZ, not pins
                     "PB2","PE15","PC2_C","PC3_C"}   #spare pins broken out to test pads
    extra   = sorted(gpio_used - hwdef_pins - OUTSIDE_HWDEF)

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
    #the PLL shipped with its loop filter hanging off CPOUT and VTUNE on a capacitor of its own
    print("\n=== MAX2112 tuner: PLL loop filter and gain control ===")
    MAX2112 = ('[D] MAX2112 datasheet, Pin Description: "VTUNE: connect the PLL loop filter '
               'output directly to this pin"; "CPOUT: connect to the PLL loop filter input"; '
               '"GC1: 0.5 V to 2.7 V operating range". Typical Application Circuit: shunt C '
               'and series R-C at CPOUT, series R to VTUNE, shunt C at VTUNE.')
    for ref in [r for r, v in comps.items() if v.startswith("MAX2112")]:
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    #d/L parts KiCad's Device library cannot corroborate
    "LED": (
        "0603 LED: pin 1 is the cathode and pin 2 the anode, the same polarity the "
        "vendored 0603 LED footprint marks; the board sinks pin 1 (LED0_K/LED1_K) "
        "with pin 2 on +3V3, so the LED lights when the MCU pulls low",
        "2 used pins: 1 = K, 2 = A", "2026-10-01"),
    "L": (
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        "Nexperia PESD2CANFD24LT-Q datasheet, SOT-23 pinout: pins 1 and 2 are the two "
        "protected lines and pin 3 is the common/GND (the sheet measures capacitance "
        "'from pin 1 or 2 to pin 3')",
        "all 3 pins: 1 = I/O1 (CANH), 2 = I/O2 (CANL), 3 = common (GND). The vendored "
        "symbol's combined 1=C/2=C/3=A common-node topology matches a device that "
        "clamps each line to the shared pin 3",
        "2026-10-01"),
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

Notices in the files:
README.md:
License: MIT
